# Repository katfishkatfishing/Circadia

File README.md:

# Circadia
> Third Space Hack Club Week 4!

**Circadia**, an environmental and human presence monitoring smart device, it turns on when it detects the presence of someone and the light vibe is based on the surrounding atmosphere.

## 💠 Project Overview 💠
This weeks project theme is "Autumn", and so we thought, "Hmm, what hardware things can we make with this theme?" and then someone said autumn reminds him of Halloween and pumpkin spice so we thought of a pumpkin emitting light, or some sort of nightlight (something like a Jack-o'-lantern🎃). Ofc, Autumn is quite a chilly month, might as well get some room temperature sensor, light sensor & humidty sensor while going on with the pumpkin theme. Anyways, Circadia. It can feel if there's people then it will turn on and shine light, then can change colour too.  

<i>*Note from other guy (guy2): It can also do some astronomical math to calculate sun position and change the light to match it.  

<b>+</b>Monitors dry indoor air.  

<b>+</b>The light scales off the light from the environment!!</i>

### Key Features 🗝️
---
<ul style="margin-top: -10px; margin-bottom: 0; padding-left: 30px">
    <li style="margin-bottom: 5px">
        <b>Calculates Solar Ephemeris</b>
        <ul style="padding-left: 45px">
            <p style="margin-left: -30px; margin-bottom: 5px">Fancy way of saying position of the sun.</p>
        </ul>
    </li>
    <li style="margin-bottom: 5px">
        <b>Vapor Pressure Deficit Monitoring</b>
        <ul style="padding-left: 45px">
            <p style="margin-left: -30px; margin-bottom: 5px">Humidity monitor. 🙏</p>
        </ul>
    </li>
    <li style="margin-bottom: 5px">
        <b>Fractional Brownian Motion for Ambient Light</b>
        <ul style="padding-left: 45px">
            <p style="margin-left: -30px; margin-bottom: 5px">Random light patterns uses Perlin noise.</p>
        </ul>
    </li>
    <li style="margin-bottom: 5px">
        <b>Light Sensor</b>
        <ul style="padding-left: 45px">
            <p style="margin-left: -30px; margin-bottom: 5px">This the thing to make the light brighter or dimmer depending on surroundings.</p>
        </ul>
    </li>
    <li style="margin-bottom: 5px">
        <b>Motion Sensor</b>
        <ul style="padding-left: 45px">
            <p style="margin-left: -30px; margin-bottom: 5px">Detects stuff to auto on and off.</p>
        </ul>
    </li>
    <li style="margin-bottom: 5px">
        <b>LCD Display</b>
        <ul style="padding-left: 45px">
            <p style="margin-left: -30px; margin-bottom: 5px">Cool display firmware that guy2 did.</p>
        </ul>
    </li>
    <li style="margin-bottom: 5px">
        <b>Halloween Festive Feel</b>
        <ul style="padding-left: 45px">
            <p style="margin-left: -30px; margin-bottom: 5px">Can feel halloween-y with this thing in living room.</p>
        </ul>
    </li>
</ul>

## Photos
---
<table>
  <tr>
    <td align="center">
      <br>
      Schematic
    </td>
  </tr>
</table>
<table>
  <tr>
    <td align="center">
       <br>
      PCB Trace Routing
    </td>
    <td align="center">
      <br>
      3D PCB Render
    </td>
  </tr>
</table>

<b><u>Circadia 3D Model</u></b>
<table>
  <tr>
    <td align="center">
       <br>
    </td>
    <td align="center">
      <br>
    </td>
  </tr>
  <tr>
    <td align="center">
       <br>
    </td>
    <td align="center">
      <br>
    </td>
  </tr>
</table>

## BOM
| Reference                             | Qty | Value                       | Exclude from Board | Footprint                                                  | Package                | Price        | Check_prices                                                                                          |
| ------------------------------------- | --- | --------------------------- | ------------------ | ---------------------------------------------------------- | ---------------------- | ------------ | ----------------------------------------------------------------------------------------------------- |
| C1                                    | 1   | 1uF                         |                    | Capacitor_SMD:C_0402_1005Metric                            | Cut Tape (1 Unit)      | $0.02        | https://www.google.com/search?q=https://www.aliexpress.com/w/wholesale-1uf-0402-capacitor.html        |
| C2,C5,C6,C7,C8,C9,C10,C11,C12,C13,C14 | 11  | 0.1uF                       |                    | Capacitor_SMD:C_0201_0603Metric                            | Reel / Pack of 100     | $1.20 / pack | https://www.google.com/search?q=https://www.aliexpress.com/w/wholesale-0.1uf-0603-capacitor.html      |
| C3                                    | 1   | 10uF                        |                    | Capacitor_SMD:C_0402_1005Metric                            | Cut Tape (1 Unit)      | $0.02        | https://www.google.com/search?q=https://www.aliexpress.com/w/wholesale-10uf-0402-capacitor.html       |
| C4                                    | 1   | 4.7uF                       |                    | Capacitor_SMD:C_0402_1005Metric                            | Cut Tape (1 Unit)      | $0.02        | https://www.google.com/search?q=https://www.aliexpress.com/w/wholesale-4.7uf-0402-capacitor.html      |
| D1,D2,D3,D4,D5,D6                     | 6   | SK6812                      |                    | LED_SMD:LED_OPSCO_SK6812_PLCC4_5.0x5.0mm_P3.1mm            | SMD-4 (Pack of 10)     | $1.50 / pack | https://www.google.com/search?q=https://www.aliexpress.com/w/wholesale-sk6812-led.html                |
| J1                                    | 1   | Conn_01x07_Socket           |                    | Connector_PinSocket_1.00mm:PinSocket_1x07_P1.00mm_Vertical | Single Unit (1x7 Pin)  | $0.10        | https://www.google.com/search?q=https://www.aliexpress.com/w/wholesale-usb-c-receptacle-16p.html      |
| J2                                    | 1   | USB_C_Receptacle_USB2.0_16P |                    | Connector_USB:USB_C_Receptacle_GCT_USB4110                 | SMD 16-Pin (Pack of 5) | $0.80 / pack | https://www.google.com/search?q=https://www.aliexpress.com/w/wholesale-usb-c-receptacle-16p.html      |
| R1,R2                                 | 2   | 5k1                         |                    | Resistor_SMD:R_0402_1005Metric                             | Reel / Pack of 100     | $0.90 / pack | https://www.google.com/search?q=https://www.aliexpress.com/w/wholesale-5.1k-resistor-0402.html        |
| R3,R4                                 | 2   | 4k7                         |                    | Resistor_SMD:R_0402_1005Metric                             | Reel / Pack of 100     | $0.90 / pack | https://www.google.com/search?q=https://www.aliexpress.com/w/wholesale-4.7k-resistor-0402.html        |
| R5                                    | 1   | 10k                         |                    | Resistor_SMD:R_0402_1005Metric                             | Reel / Pack of 100     | $0.90 / pack | https://www.google.com/search?q=https://www.aliexpress.com/w/wholesale-10k-resistor-0402.html         |
| R7                                    | 1   | 1k                          |                    | Resistor_SMD:R_0402_1005Metric                             | Reel / Pack of 100     | $0.90 / pack | https://www.google.com/search?q=https://www.aliexpress.com/w/wholesale-1k-resistor-0402.html          |
| R8                                    | 1   | 330                         |                    | Resistor_SMD:R_0402_1005Metric                             | Reel / Pack of 100     | $0.90 / pack | https://www.google.com/search?q=https://www.aliexpress.com/w/wholesale-330-ohm-resistor-0402.html     |
| SW1                                   | 1   | SW_Push                     |                    | Button_Switch_THT:SW_PUSH_1P1T_6x3.5mm_H4.3_APEM_MJTP1243  | Pack of 10             | $0.50 / pack | https://www.google.com/search?q=https://shopee.com.my/search%3Fkeyword%3Dtactile%2520switch%25206x3.5 |
| U1                                    | 1   | ESP32-S3-WROOM-2            |                    | RF_Module:ESP32-S3-WROOM-2                                 | Single Unit            | $5.60        | https://www.aliexpress.com/item/1005004543881248.html                                                 |
| U2                                    | 1   | TPS7133                     |                    | Package_SO:SOIC-8_3.9x4.9mm_P1.27mm                        | Single Unit            | $0.40        | https://www.google.com/search?q=https://www.aliexpress.com/w/wholesale-tps7133.html                   |
| U3                                    | 1   | AHT20                       |                    | Footprint:PSON100P300X300X110-6N                           | DFN-6 (Single Unit)    | $0.45        | https://www.aliexpress.com/w/wholesale-aht20.html                                                     |
| U4                                    | 1   | HLK-LD2410C                 |                    | Footprint:MODULE_HLK-LD2410C                               | Module Board           | $3.50        | https://www.aliexpress.com/item/1005006213777827.html                                                 |
| U5                                    | 1   | BH1750FVI-TR                |                    | Footprint:XDCR_BH1750FVI-TR                                | SMD-6 / WSOF6          | $0.50        | https://www.aliexpress.com/w/wholesale-bh1750.html                                                    |
| U6                                    | 1   | SN74HCT125N                 |                    | Footprint:N14                                              | TSSOP-14 / SOIC-14     | $0.15        | https://www.google.com/search?q=https://www.aliexpress.com/w/wholesale-sn74hct125.html                |
|-|1|1.54inch LCD Module|✅|-|-|$9.49|https://www.waveshare.com/1.54inch-lcd-module.htm|

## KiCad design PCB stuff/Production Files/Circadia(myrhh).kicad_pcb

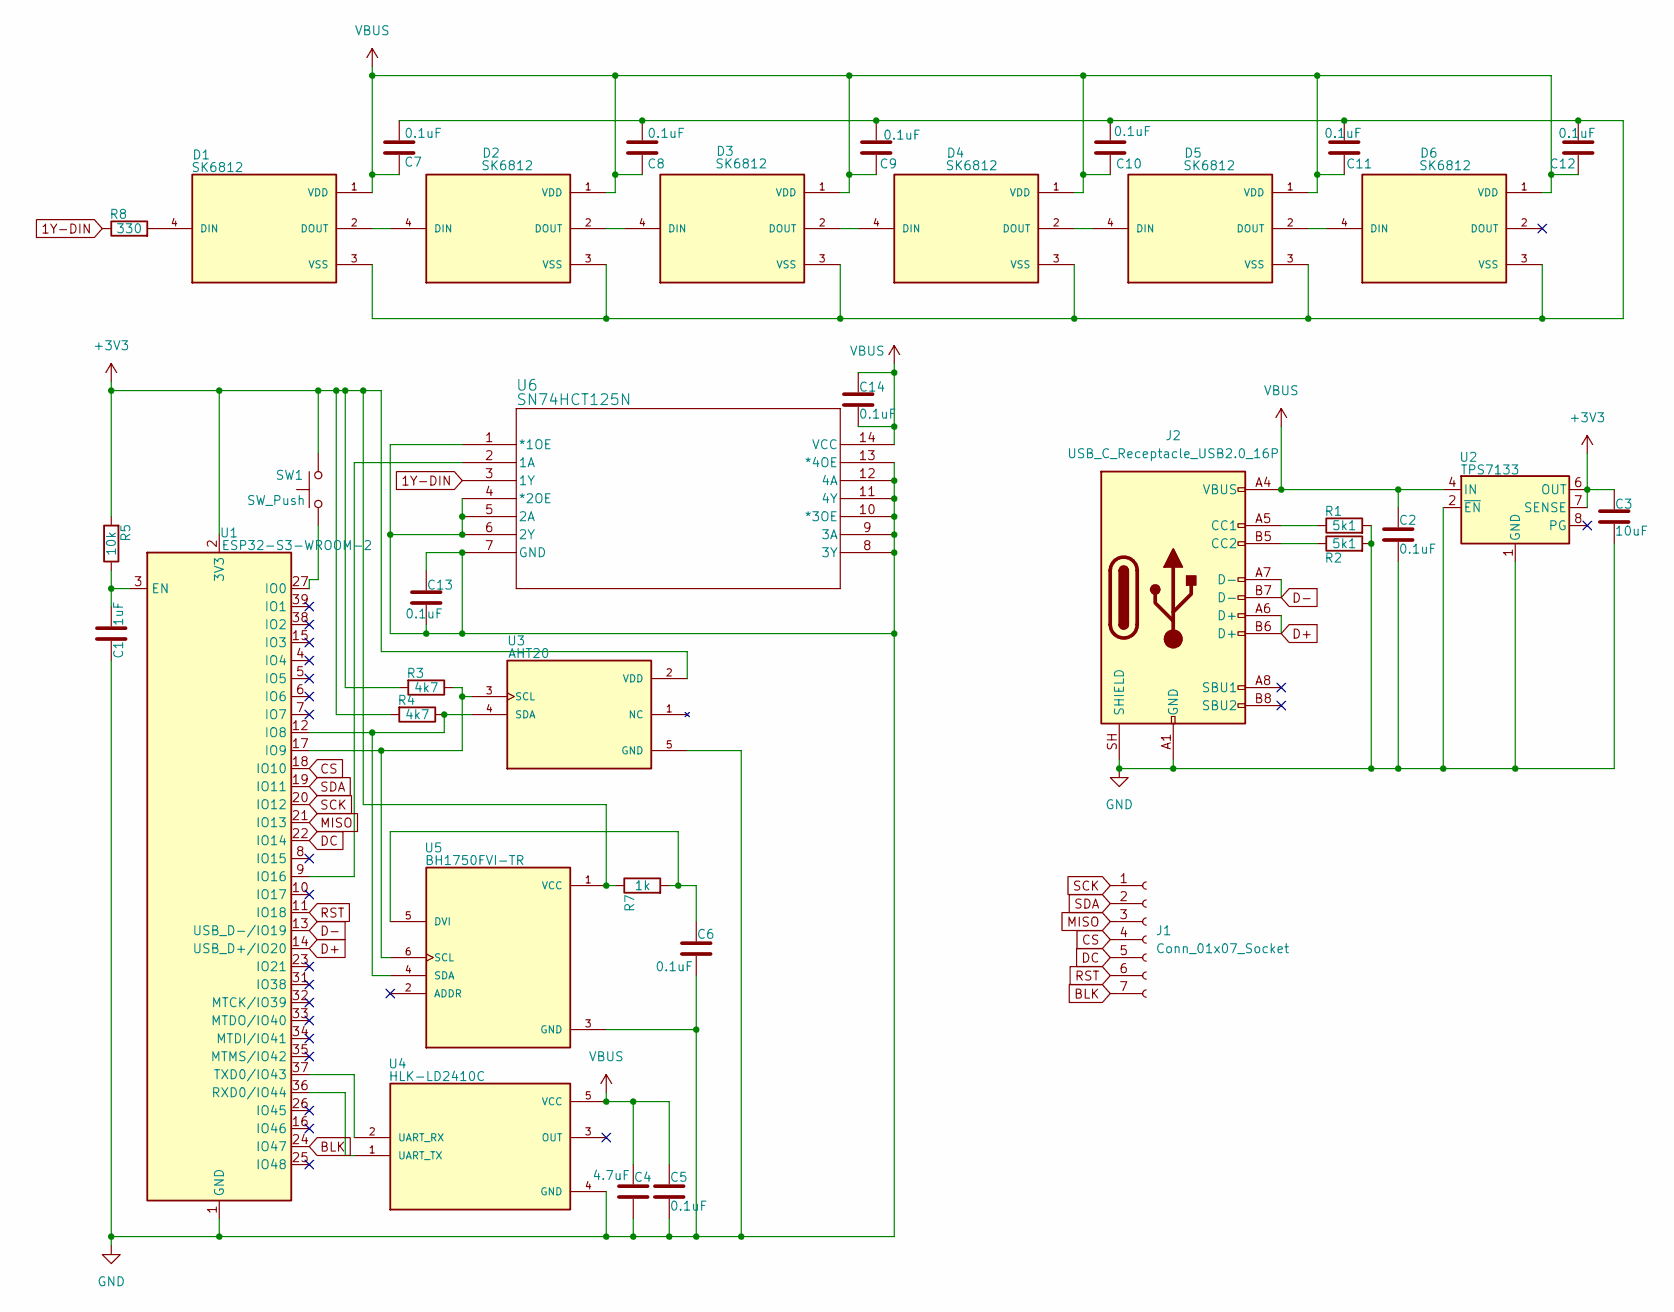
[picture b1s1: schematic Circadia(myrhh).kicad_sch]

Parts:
C1: 1uF; C_0402_1005Metric
C2, C5, C6, C7, C8, C9, C10, C11, C12, C13, C14: 0.1uF; C_0201_0603Metric
C3: 10uF; C_0402_1005Metric
C4: 4.7uF; C_0402_1005Metric
D1, D2, D3, D4, D5, D6: SK6812; LED_OPSCO_SK6812_PLCC4_5.0x5.0mm_P3.1mm; PARTREV 03
J1: Conn_01x07_Socket; PinSocket_1x07_P1.00mm_Vertical
J2: USB_C_Receptacle_USB2.0_16P; USB_C_Receptacle_GCT_USB4110
R1, R2: 5k1; R_0402_1005Metric
R3, R4: 4k7; R_0402_1005Metric
R5: 10k; R_0402_1005Metric
R7: 1k; R_0402_1005Metric
R8: 330; R_0402_1005Metric
SW1: SW_Push; SW_PUSH_1P1T_6x3.5mm_H4.3_APEM_MJTP1243
U1: ESP32-S3-WROOM-2
U2: TPS7133; SOIC-8_3.9x4.9mm_P1.27mm
U3: AHT20; PSON100P300X300X110-6N; PARTREV V1.0
U4: HLK-LD2410C; MODULE_HLK-LD2410C; PARTREV V1.00
U5: BH1750FVI-TR; XDCR_BH1750FVI-TR; PARTREV D
U6: SN74HCT125N; N14

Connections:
1Y-DIN: R8.1, U6.3 (1Y)
+3V3: C3.1, R3.2, R4.2, R5.2, R7.1, SW1.2, U1.2 (3V3), U2.5 (OUT), U2.6 (OUT), U2.7 (SENSE), U3.2 (VDD), U5.1 (VCC)
BLK: J1.7, U1.24 (IO47)
CS: J1.4, U1.18 (IO10)
D+: J2.A6 (D+), J2.B6 (D+), U1.14 (USB_D+/IO20)
D-: J2.A7 (D-), J2.B7 (D-), U1.13 (USB_D-/IO19)
DC: J1.5, U1.22 (IO14)
GND: C1.1, C2.2, C3.2, C4.2, C5.2, C6.2, C13.1, C13.2, J2.A1 (GND), J2.A12 (GND), J2.B1 (GND), J2.B12 (GND), J2.SH (SHIELD), R1.2, R2.2, U1.1 (GND), U1.40 (GND), U1.41 (GND), U2.1 (GND), U2.2 (~EN), U3.5 (GND), U4.4 (GND), U5.3 (GND), U6.1 (*1OE), U6.4 (*2OE), U6.5 (2A), U6.6 (2Y), U6.7 (GND), U6.8 (3Y), U6.9 (3A), U6.10 (*3OE), U6.11 (4Y), U6.12 (4A), U6.13 (*4OE)
MISO: J1.3, U1.21 (IO13)
unnamed: D1.4 (DIN), R8.2
unnamed: D1.2 (DOUT), D2.4 (DIN)
unnamed: C7.2, C8.2, C9.2, C10.2, C11.2, C12.2, D1.3 (VSS), D2.3 (VSS), D3.3 (VSS), D4.3 (VSS), D5.3 (VSS), D6.3 (VSS)
unnamed: D2.2 (DOUT), D3.4 (DIN)
unnamed: D3.2 (DOUT), D4.4 (DIN)
unnamed: D4.2 (DOUT), D5.4 (DIN)
unnamed: D5.2 (DOUT), D6.4 (DIN)
unnamed: J2.A5 (CC1), R1.1
unnamed: J2.B5 (CC2), R2.1
unnamed: C1.2, R5.1, U1.3 (EN)
unnamed: SW1.1, U1.27 (IO0)
unnamed: R4.1, U1.12 (IO8), U3.4 (SDA), U5.4 (SDA)
unnamed: R3.1, U1.17 (IO9), U3.3 (SCL), U5.6 (SCL)
unnamed: U1.9 (IO16), U6.2 (1A)
unnamed: U1.36 (RXD0/IO44), U4.1 (UART_TX)
unnamed: U1.37 (TXD0/IO43), U4.2 (UART_RX)
unnamed: C6.1, R7.2, U5.5 (DVI)
RST: J1.6, U1.11 (IO18)
SCK: J1.1, U1.20 (IO12)
SDA: J1.2, U1.19 (IO11)
VBUS: C2.1, C4.1, C5.1, C7.1, C8.1, C9.1, C10.1, C11.1, C12.1, C14.1, C14.2, D1.1 (VDD), D2.1 (VDD), D3.1 (VDD), D4.1 (VDD), D5.1 (VDD), D6.1 (VDD), J2.A4 (VBUS), J2.A9 (VBUS), J2.B4 (VBUS), J2.B9 (VBUS), U2.3 (IN), U2.4 (IN), U4.5 (VCC), U6.14 (VCC)

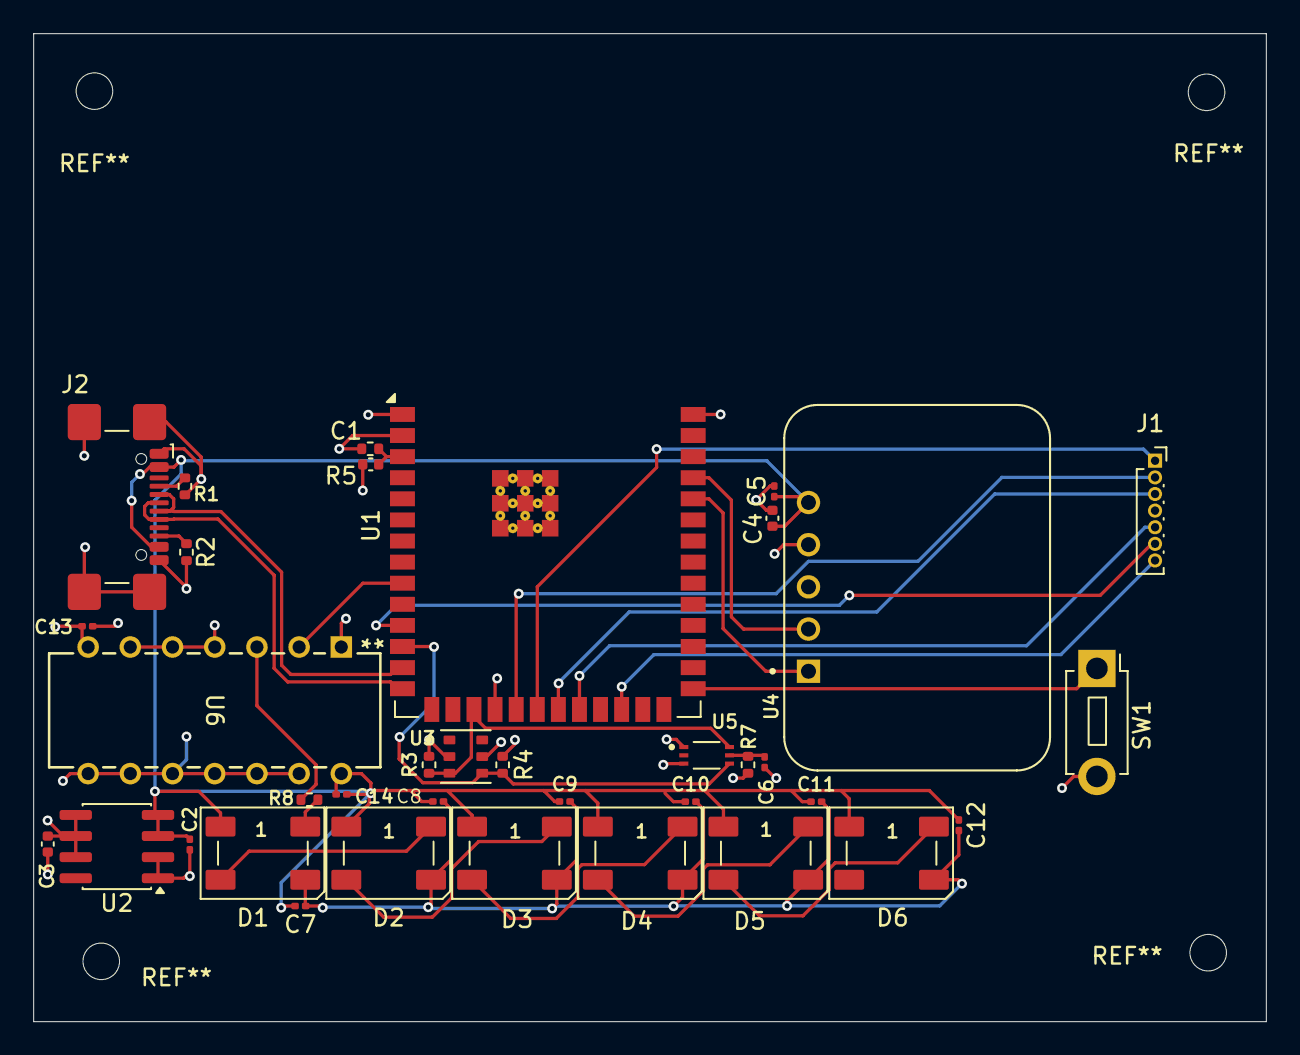
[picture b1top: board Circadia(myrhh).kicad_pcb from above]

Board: 4 copper layers, 74.2 x 59.5 mm, 36 parts (0 on the bottom side), 30 nets.
